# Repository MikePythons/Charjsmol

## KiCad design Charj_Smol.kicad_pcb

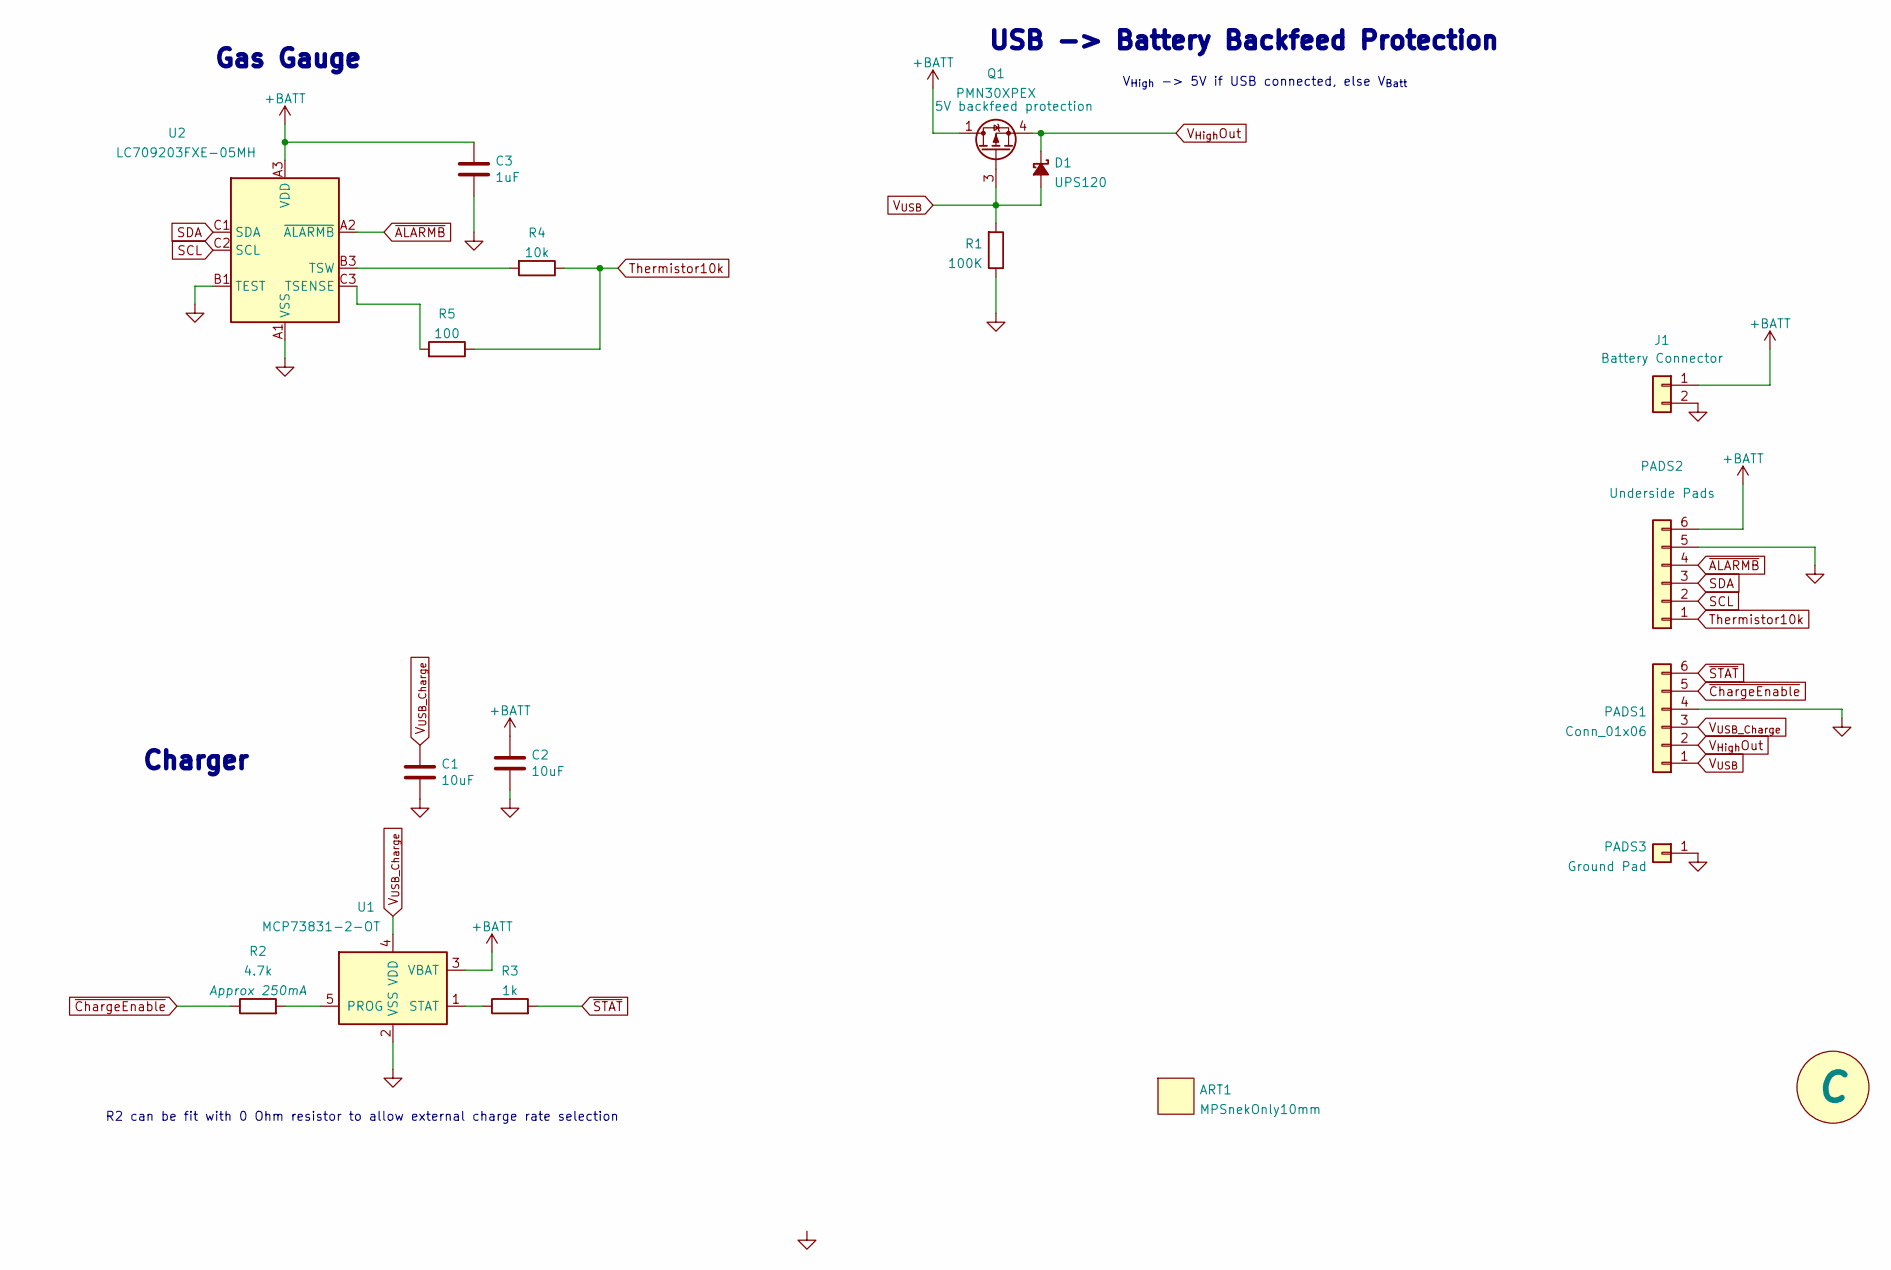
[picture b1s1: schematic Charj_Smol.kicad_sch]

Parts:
ART1: MPSnekOnly10mm; MPSnekOnly_10x6mm
C1, C2: 10uF; C_0603_1608Metric
C3: 1uF; C_0603_1608Metric
D1: UPS120; UPS120_D_Powermite_AK
J1: Battery Connector; JST_PH_S2B_B2B_Vers
MISC1: C; RevisionSymbol_Small
PADS1: Conn_01x06; EdgePad_1x06
PADS2: Underside Pads; EdgePad_1x06
PADS3: Ground Pad; GND_PAD
Q1: PMN30XPEX; TSOP-6_1.65x3.05mm_P0.95mm
R1: 100K; R_0402_1005Metric
R2: 4.7k; R_0603_1608Metric_Pad0.98x0.95mm_HandSolder
R3: 1k; R_0402_1005Metric
R4: 10k; R_0402_1005Metric
R5: 100; R_0402_1005Metric
U1: MCP73831-2-OT; SOT-23-5
U2: LC709203FXE-05MH; WLCSP9-1.60x1.76mm

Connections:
+BATT: C2.1, C3.1, J1.1, PADS2.6, Q1.1 (D), Q1.2 (D), Q1.5 (D), Q1.6 (D), U1.3 (VBAT), U2.A3 (VDD)
GND: C1.2, C2.2, C3.2, J1.2, PADS1.4, PADS2.5, PADS3.1, R1.1, U1.2 (VSS), U2.A1 (VSS), U2.B1 (TEST)
unnamed: R2.2, U1.5 (PROG)
unnamed: R3.1, U1.1 (STAT)
unnamed: R4.2, U2.B3 (TSW)
unnamed: R5.2, U2.C3 (TSENSE)
SCL: PADS2.2, U2.C2 (SCL)
SDA: PADS2.3, U2.C1 (SDA)
Thermistor10k: PADS2.1, R4.1, R5.1
V_{High}Out: D1.1 (K), PADS1.2, Q1.4 (S)
V_{USB_Charge}: C1.1, PADS1.3, U1.4 (VDD)
V_{USB}: D1.2 (A), PADS1.1, Q1.3 (G), R1.2
~ALARMB: PADS2.4, U2.A2 (~ALARMB)
~ChargeEnable: PADS1.5, R2.1
~STAT: PADS1.6, R3.2

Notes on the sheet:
R2 can be fit with 0 Ohm resistor to allow external charge rate selection
USB -> Battery Backfeed Protection
Gas Gauge
V_{High} -> 5V if USB connected, else V_{Batt}
Charger

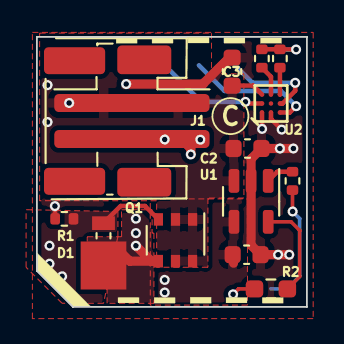
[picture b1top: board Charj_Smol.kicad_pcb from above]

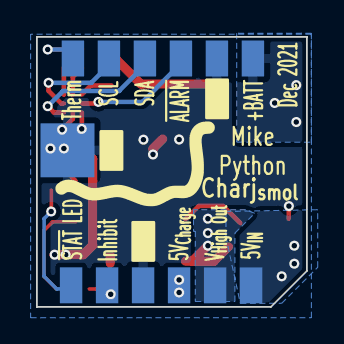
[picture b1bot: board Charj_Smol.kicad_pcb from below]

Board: 2 copper layers, 15.0 x 15.0 mm, 18 parts (4 on the bottom side), 15 nets.

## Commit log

2021-12-24 Revision C
    - Fixed battery connector polarity
    - Added silkscreen marks to help align bottom pads with footprint when placing on carrier board
2021-12-24 Silkscreen tidying; still Rev C
2021-12-24 Adding image
2021-12-24 Forgot to save board before previous commit. Moving RevC marker to this commit.
